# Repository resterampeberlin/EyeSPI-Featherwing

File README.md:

# Purpose

# Credits

This open source code project is has been proudfully produced in Berlin (and other places around the globe) by

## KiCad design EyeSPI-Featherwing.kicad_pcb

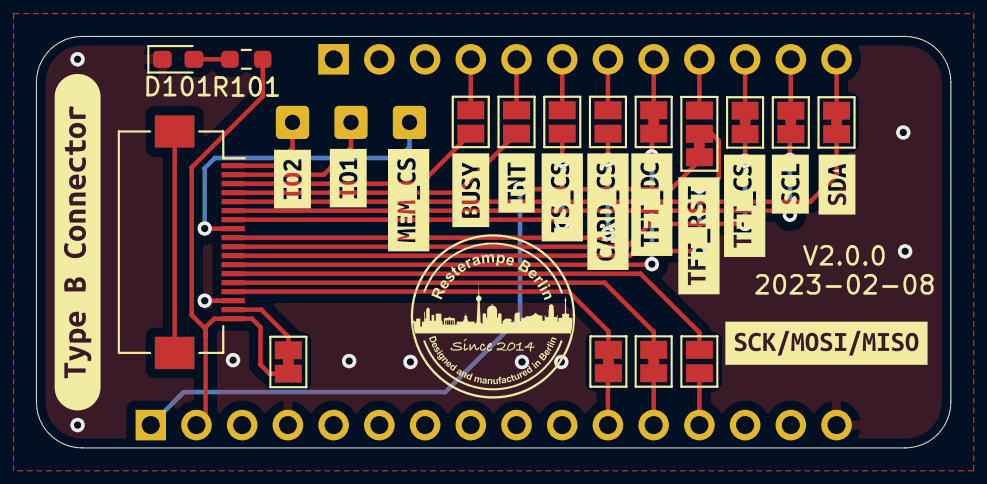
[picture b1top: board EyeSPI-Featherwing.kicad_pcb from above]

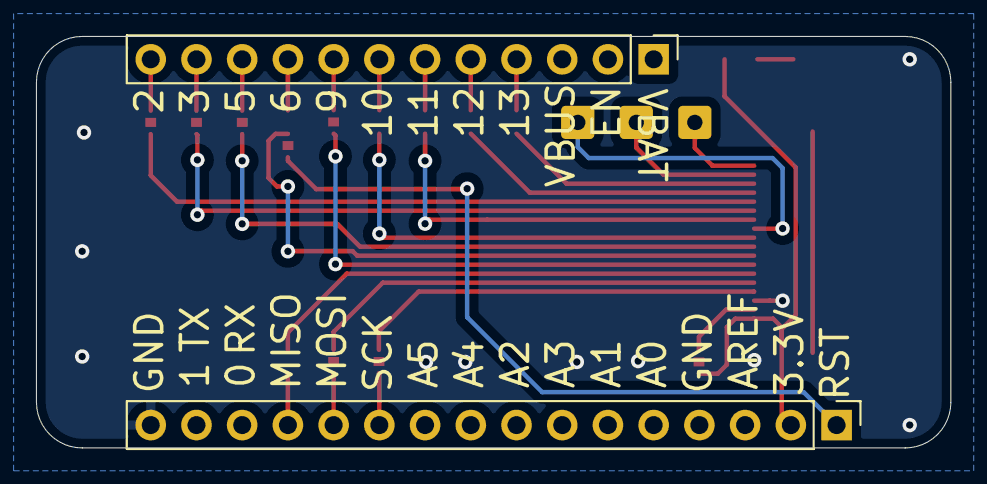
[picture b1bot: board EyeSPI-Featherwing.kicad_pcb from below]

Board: 2 copper layers, 50.8 x 22.9 mm, 35 parts (2 on the bottom side), 32 nets.

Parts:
D101: LED; LED_0603_1608Metric_Pad1.05x0.95mm_HandSolder
J101: Conn_01x16; PinHeader_1x16_P2.54mm_Vertical
J102: Conn_01x12; PinHeader_1x12_P2.54mm_Vertical
J106: EYE_SPI_DISPLAY_TYPE_B; Hirose_FH12-18S-0.5SH_1x18-1MP_P0.50mm_Horizontal
J107, J108, J109: Conn_01x01; SolderWire-0.25sqmm_1x01_D0.65mm_OD1.7mm
JP101, JP102, JP104, JP105, JP107, JP108, JP109: SolderJumper_2_Bridged; SolderJumper-2_P1.3mm_Bridged_Pad1.0x1.5mm
JP103, JP106, JP111, JP112, JP113: SolderJumper_2_Open; SolderJumper-2_P1.3mm_Open_Pad1.0x1.5mm
JP110: SolderJumper_3_Bridged12; SolderJumper-3_P1.3mm_Bridged12_Pad1.0x1.5mm_NumberLabels
R101: 1K; R_0603_1608Metric_Pad0.98x0.95mm_HandSolder
kibuzzard-63C5DCBF: G***; kibuzzard-63C5DCBF
kibuzzard-63C5DCD9: G***; kibuzzard-63C5DCD9
kibuzzard-63C5DCE3: G***; kibuzzard-63C5DCE3
kibuzzard-63C5DCEE: G***; kibuzzard-63C5DCEE
kibuzzard-63C5DCF9: G***; kibuzzard-63C5DCF9
kibuzzard-63C5DD0E: G***; kibuzzard-63C5DD0E
kibuzzard-63C5DD7B: G***; kibuzzard-63C5DD7B
kibuzzard-63C5DD9E: G***; kibuzzard-63C5DD9E
kibuzzard-63C5DD88: G***; kibuzzard-63C5DD88
kibuzzard-63C5DD93: G***; kibuzzard-63C5DD93
kibuzzard-63C5DDAE: G***; kibuzzard-63C5DDAE
kibuzzard-63C5DDB7: G***; kibuzzard-63C5DDB7
kibuzzard-63C5DE01: G***; kibuzzard-63C5DE01
kibuzzard-63E91F4E: G***; kibuzzard-63E91F4E

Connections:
+3V3: J101.2, J106.18 (VCC), JP102.2 (B), R101.1
/5: J102.10, JP105.2 (B)
/6: J102.9, JP110.3 (B)
/9: J102.8, JP108.2 (B)
/10: J102.7, JP112.2 (B)
/11: J102.6, JP103.2 (B)
/12: J102.5, JP106.2 (B)
/13: J102.4, JP113.2 (B)
/BUSY: J106.3 (BUSY/TE), JP113.1 (A)
/EYESPI_MISO: J106.13 (MISO), JP111.1 (A)
/EYESPI_MOSI: J106.14 (MOSI), JP109.1 (A)
/EYESPI_SCK: J106.15 (SCK), JP107.1 (A)
/EYESPI_SCL: J106.6 (SCL), JP104.1 (A)
/EYESPI_SDA: J106.5 (SDA), JP101.1 (A)
/GPIO1: J106.2 (GPIO1), J107.1
/GPIO2: J106.1 (GPIO2), J108.1
/INT: J106.4 (INT), JP106.1 (A)
/LITE: J106.17 (BL), JP102.1 (A)
/MISO: J101.13, JP111.2 (B)
/MOSI: J101.12, JP109.2 (B)
/SCK: J101.11, JP107.2 (B)
/SCL: J102.11, JP104.2 (B)
/SDA: J102.12, JP101.2 (B)
/TFT_DC: J106.12 (DC), JP108.1 (A)
/~CARD_CS: J106.9 (~SD_CS), JP112.1 (A)
/~MEM_CS: J106.8 (~MEM_CS), J109.1
/~RST: J101.1, JP110.1 (A)
/~TFT_CS: J106.10 (~DISP_CS), JP105.1 (A)
/~TFT_RST: J106.11 (~RESET), JP110.2 (C)
/~TS_CS: J106.7 (~TS_CS), JP103.1 (A)
GND: D101.1 (K), J101.4, J101.16, J106.16 (GND)
unnamed: D101.2 (A), R101.2

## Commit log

2023-01-17 Initial version
2023-01-21 Production
2023-01-21 Documentation updated
2023-02-09 Closed #1

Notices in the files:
EyeSPI-Featherwing.kicad_pcb:
https://creativecommons.org/licenses/by-nc/4.0
License CC BY-NC 4.0
